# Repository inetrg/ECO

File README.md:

# Source Files for the ECO Sensor Box
The ECO sensor box is a versatile modular wireless sensor box for perpetual operation based on energy harvesting.
Using a self-adaptive power management the sensor self-adapts its power consumption according to energy availability,
based on real-time, online self measurement of its power consumption and availability.

This repository contains source and design files required to build your own ECO-enabled sensor box.
The initial version of the ECO box used separate independent modules which you can find in corresponding subfolders.
The newer version uses a more integrated approach by placing most of the subsystems onto a single PCB for easier setup.

## ECO Box Design Files
Below we list some notes on what to consider when working with the ECO Box design files.

## Tools and Files
All design files are being processed only using open source tools to make them accessible and reusable for everyone.

KiCAD is used for schematics and Layout of the custom PCB.
FreeCAD is used for mechanical design of the physical box assembly, including the enclosure, PCB, external sensors, antenna, etc.
Blender is used for further visualization/rendering purposes (custom materials, lighting etc.) for more sophisticated controls of visuals.

To exchange data between all these tools different formats are used and some of them need workarounds to make everything work as expected.

### FreeCAD -> KiCAD
As mentioned, FreeCAD is used for the mechanical part. So an easy way to get a fitting PCB outline for a given enclosure is to export the outline from there to KiCAD.
For this the DXF 2D export of FreeCAD is used and the exported drawing is then imported to the edge.cuts layer in KiCAD before doing the PCB layout.

For custom components that don't have a 3D-Symbol in KiCAD, we also use FreeCAD to desing them and use the STEP export to use them in KiCAD.

### KiCAD -> FreeCAD
With the PCB being done the whole PCB including associated 3D models for components can be imported from the *.kicad_pcb file using the KiCADStepUp Workbench of FreeCAD.
For this the "Load KiCAD PCB and Board Parts" was used.
A special case that required a workaround here was the "Add Tracks" feature that didn't work well and made FreeCAD crash frequently.
Instead the Tracks were exported to DXF from KiCAD and then imported using the "Add Silks" feature (custom colors can still be appied later on).

In FreeCAD any missing mechanical design can then be aligned around the PCB and its components.

### FreeCAD -> Blender
To export the whole model from FreeCAD to blender the format that worked best for us is *gltf.
However, there is a problem with colors/materials that are only applied to faces (instead of whole objects) and if exported directly to gltf the colors will disappear.
A workaround for that is to first export to "STEP with colors" then import to FreeCAD again, an then do the export to gltf for blender. This way the colors that are present on KiCAD models don't get lost.

# Third Party Material
Some CAD models of PCB components and the assembly design use third party material from [SnapEDA](https://www.snapeda.com/) and [GrabCAD](https://grabcad.com).

# Further Information
Firmware sources can be found in a [separate repository](https://github.com/inetrg/ECO-fw).
For more information also visit our [project website](https://eco.riot-apps.net).

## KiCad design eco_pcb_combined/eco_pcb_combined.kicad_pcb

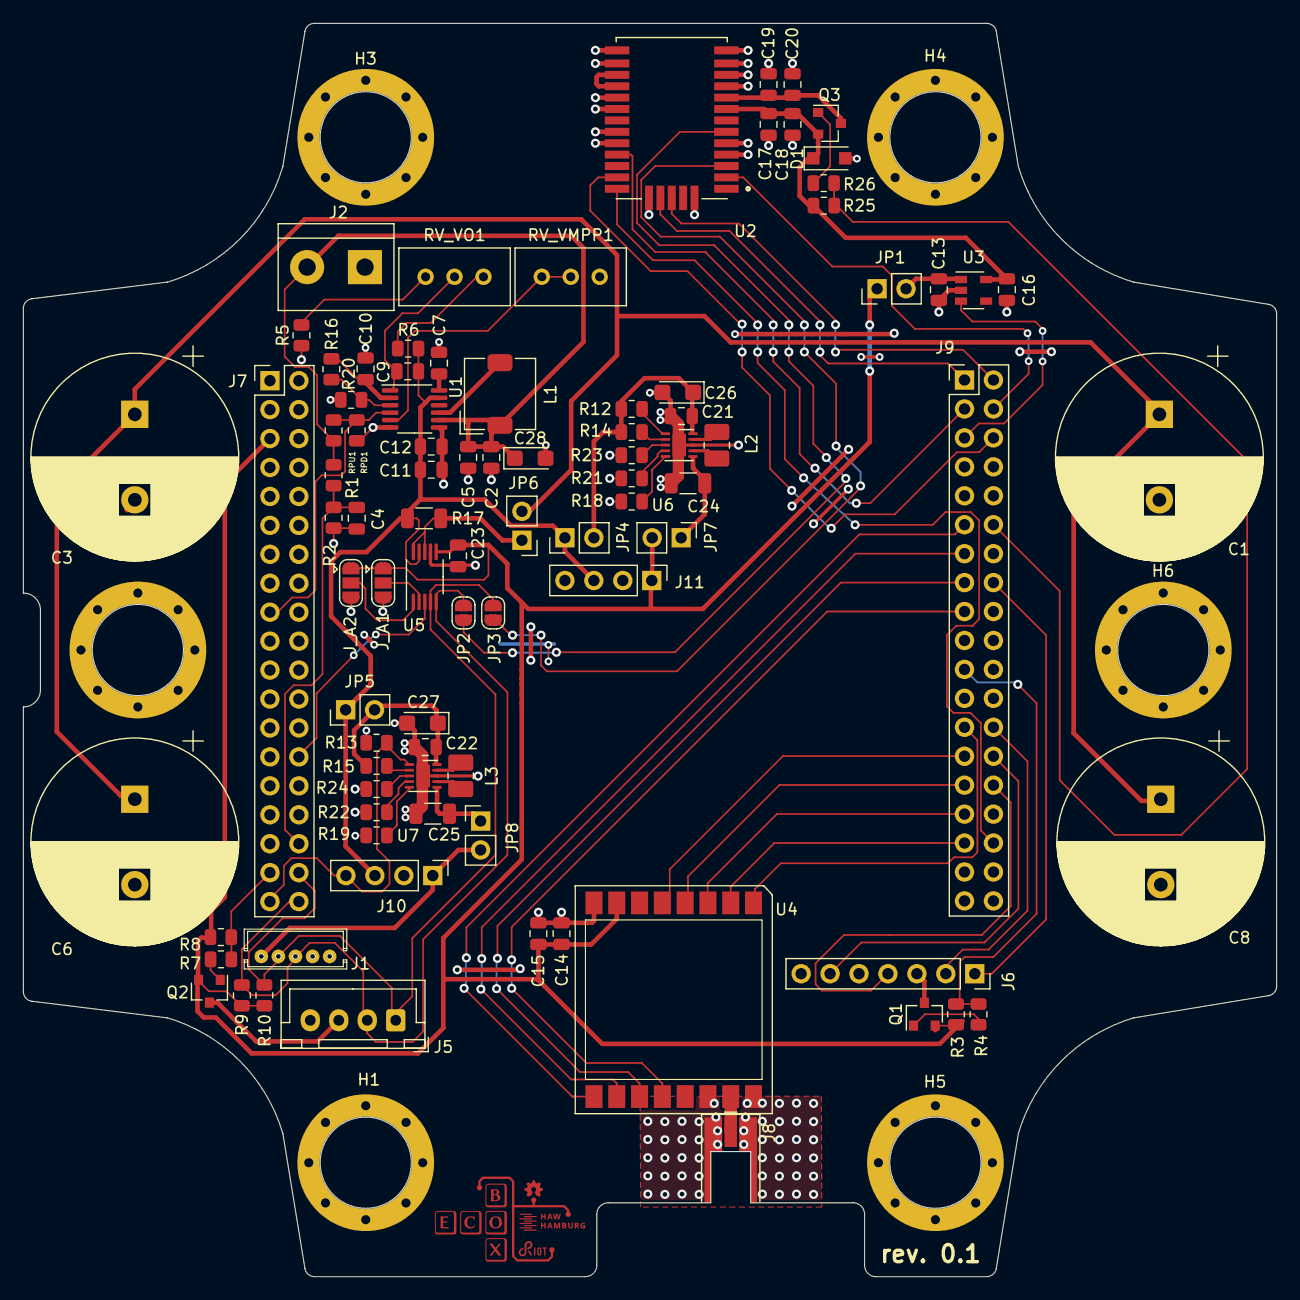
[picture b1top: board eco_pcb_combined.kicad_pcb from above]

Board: 2 copper layers, 110.0 x 110.0 mm, 97 parts (1 on the bottom side), 75 nets.

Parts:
C1, C3, C6, C8: 50F-100F; CP_Radial_D18.0mm_P7.50mm
C2, C11, C14, C20, C21, C22: 10µF; C_0805_2012Metric
C4: 1nF; C_0805_2012Metric
C5, C7, C12, C13, C16: 1µF; C_0805_2012Metric
C9: 22pF; C_0805_2012Metric
C10, C18: 4.7µF; C_0805_2012Metric
C15, C17, C19, C23: 100nF; C_0805_2012Metric
C24, C25: 22µF; C_1206_3216Metric
C26, C27, C28: 47µF; CP_EIA-3216-10_Kemet-I
D1: Littlefuse_TVS_SMF3.3; D_SOD-123F
H1, H2, H3, H4, H5, H6: MountingHole; MountingHole_8.1mm_M8_Pad_Via
J1: Conn_01x05; JST_B5B_ZR
J2: Screw_Terminal_01x02; TerminalBlock_bornier-2_P5.08mm
J5: Conn_01x04; JST_XH_B4B-XH-A_1x04_P2.50mm_Vertical
J6: BOB-00544; PinSocket_1x07_P2.54mm_Vertical
J7, J9: Conn_02x19_Odd_Even; PinHeader_2x19_P2.54mm_Vertical
J8: Conn_Coaxial; MMCX_Molex_73415-0961_Horizontal_1.6mm-PCB
J10, J11: Conn_01x04_Female; PinHeader_1x04_P2.54mm_Vertical
JP1, JP4, JP5, JP6, JP7, JP8: Jumper_2_Bridged; PinHeader_1x02_P2.54mm_Vertical
JP2, JP3: Jumper_NC_Small; SolderJumper-2_P1.3mm_Open_RoundedPad1.0x1.5mm
J_A1, J_A2: JP2E; SolderJumper-3_P1.3mm_Open_RoundedPad1.0x1.5mm
L1: 10µH; L_TDK_SLF6045
L2, L3: 2.2µH; L_1008_2520Metric_Pad1.43x2.20mm_HandSolder
LOGO1: Logo; RIOT_ECO_HAW_OSHW_straight
Q1, Q2, Q3: Si2329DS; SOT-23
R1, R16: 1MΩ; R_0805_2012Metric
R2, R5: 390kΩ; R_0805_2012Metric
R3, R8, R12, R13, R14, R15, R26: 100kΩ; R_0805_2012Metric
R4, R7, R25: 330Ω; R_0805_2012Metric
R6: 1.1MΩ; R_0805_2012Metric
R9, R10: 4.7kΩ; R_0805_2012Metric
R17: 0.27Ω; R_1206_3216Metric
R18, R19, R21, R22: 0Ω; R_0805_2012Metric
R20: 2.5MΩ; R_0805_2012Metric
R23, R24: 36.5kΩ; R_0805_2012Metric
RPD1: 100kΩ; R_0805_2012Metric
RPU1: 100kΩ; R_0805_2012Metric
RV_VMPP1: 500kΩ; Potentiometer_Bourns_3296W_Vertical
RV_VO1: 500kΩ; Potentiometer_Bourns_3296W_Vertical
U1: LTC3105; MSOP-12_3x4mm_P0.65mm
U2: L96; XCVR_L96
U3: TPS7A0230PDBVR; SOT-23-5
U4: DORJI_DRF1276G; DRF1276G
U5: INA226INA226AIDGS; VSSOP-10_3x3mm_P0.5mm
U6, U7: TPS63900; WSON-10-1EP_2.5x2.5mm_P0.5mm_EP1.2x2mm

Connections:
3V3: C14.2, C15.2, C23.2, J7.5, J11.1, JP1.1, JP7.2, J_A1.1, J_A2.1, Q1.2, Q2.2, R3.1, R8.1, R9.1, R10.1, U4.7, U5.6
3V3_EXT_I2C: J5.3, Q2.3
3V3_SDCARD: J6.3, Q1.3
3V_GPS: C16.2, C17.2, C18.2, D1.1, Q3.2, R26.1, U2.8, U3.5
5V: J1.5, J10.1, JP8.2
/IN+: JP6.1, R17.2, U5.8, U5.10
A0_PA0_WKUP1|INA_ALERT: J7.28, U5.3
A3_PB0|PV_OCV_SENSE: C4.2, J7.34, R1.1, R2.2
D2_PA10|LORA_DIO0: J9.33, U4.2
D3_PB3|LORA_DIO1: J9.31, U4.3
D4_PB5|LORA_DIO2: J9.29, U4.4
D5_PB4|LORA_DIO3: J9.27, U4.5
D6_PB10|LORA_RESET: J9.25, U4.1
D8_PA9|SDCARD_PWR_SW: J9.21, R3.2, R4.1
D10_PB6|LORA_CS: J9.17, U4.12
D11_PA7|LORA_MOSI: J9.15, U4.11
D12_PA6|LORA_MISO: J9.13, U4.10
D13_PA5|LORA_SCK_LED2: J9.11, U4.9
FBLDO: R16.1, R20.2, U1.3
GND: C1.2, C2.2, C3.2, C4.1, C5.2, C6.2, C7.1, C8.2, C10.1, C11.1, C12.1, C13.1, C14.1, C15.1, C16.1, C17.1, C18.1, C19.1, C20.1, C21.1, C22.1, C23.1, C24.1, C25.1, C26.2, C27.2, C28.2, D1.2, J1.1, J1.2, J2.1, J5.4, J6.5, J7.8, J7.19, J7.20, J7.22, J8.2, J9.9, J9.20, J10.2, J11.2, J_A1.3, J_A2.3, R2.1, R5.1, R13.2, R18.1, R19.1, R20.1, R21.1, R22.1, R23.1, R24.1, RPD1.2, RV_VMPP1.1, U1.6, U1.7, U2.4, U2.5, U2.10, U2.11, U2.12, U2.13, U2.14, U2.15, U2.18, U2.19, U2.21, U2.22, U2.27, U2.31, U3.2, U4.8, U4.14, U4.16, U5.7, U6.8, U6.11, U7.8, U7.11
LDO: C10.2, R16.2, U1.2
LORA_ANT: J8.1, U4.15
unnamed: C7.2, U1.12
unnamed: C9.1, RV_VO1.2, U1.1
unnamed: C13.2, JP1.2, U3.1
unnamed: C19.2, C20.2, Q3.3, U2.9
unnamed: C21.2, C26.1, JP4.2, R12.2, R14.2, U6.10
unnamed: C22.2, C27.1, JP5.2, R15.2, U7.10
unnamed: C24.2, JP7.1, U6.6
unnamed: C25.2, JP8.1, U7.6
unnamed: JP2.2, U2.6
unnamed: JP3.2, U2.3
unnamed: J_A1.2, U5.2
unnamed: J_A2.2, U5.1
unnamed: L1.2, U1.9
unnamed: L2.1, U6.7
unnamed: L2.2, U6.9
unnamed: L3.1, U7.7
unnamed: L3.2, U7.9
unnamed: Q1.1, R4.2
unnamed: Q2.1, R7.2
unnamed: Q3.1, R25.2
unnamed: R5.2, RV_VO1.3
unnamed: R6.2, RV_VO1.1
unnamed: R12.1, U6.1
unnamed: R14.1, U6.2
unnamed: R15.1, U7.2
unnamed: R18.2, U6.5
unnamed: R19.2, U7.5
unnamed: R21.2, U6.4
unnamed: R22.2, U7.4
unnamed: R23.2, U6.3
unnamed: R24.2, U7.3
unnamed: RV_VMPP1.2, RV_VMPP1.3, U1.5
unnamed: U2.16, U2.17
PA12: J9.12, R25.1, R26.2
PA15|LTC_SHDN: J7.17, RPD1.1, RPU1.1, U1.4
PB8_D15|GPS_NRESET: J9.3, U2.23
PB9_D14|GPS_SUP_EN: J9.5, U3.3
PB12|SDCARD_CS: J6.1, J9.16
PB13|SDCARD_SCK: J6.4, J9.30
PB14|SDCARD_MISO: J6.6, J9.28
PB15|SDCARD_MOSI: J6.2, J9.26
PC0|I2C_SCL: J1.3, J5.2, J7.38, JP2.1, R9.2, U5.5
PC1|I2C_SDA: J1.4, J5.1, J7.36, JP3.1, R10.2, U5.4
PC2|EXT_SENS_3V3_SW: J7.35, R7.1, R8.2
PC3|5V_EN: J7.37, J10.4, R13.1, U7.1
PC4|GPS_UART_RX_U1TX: J9.34, U2.26
PC5|GPS_UART_TX_U1RX_WKUP5: J9.6, U2.25
PC6|GPS_3D_FIX: J9.4, U2.2
PC8|GPS_TIME_PULSE: J9.2, U2.29
PC9|GPS_FORCE_ON: J9.1, U2.28
PV+: C2.1, C5.1, C28.1, J2.2, L1.1, R1.2, RPU1.2, U1.8
VSC: C1.1, C3.1, C6.1, C8.1, JP6.2
V_CHGREG: C9.2, C11.2, C12.2, J10.3, J11.3, JP4.1, JP5.1, R6.1, R17.1, U1.11, U5.9

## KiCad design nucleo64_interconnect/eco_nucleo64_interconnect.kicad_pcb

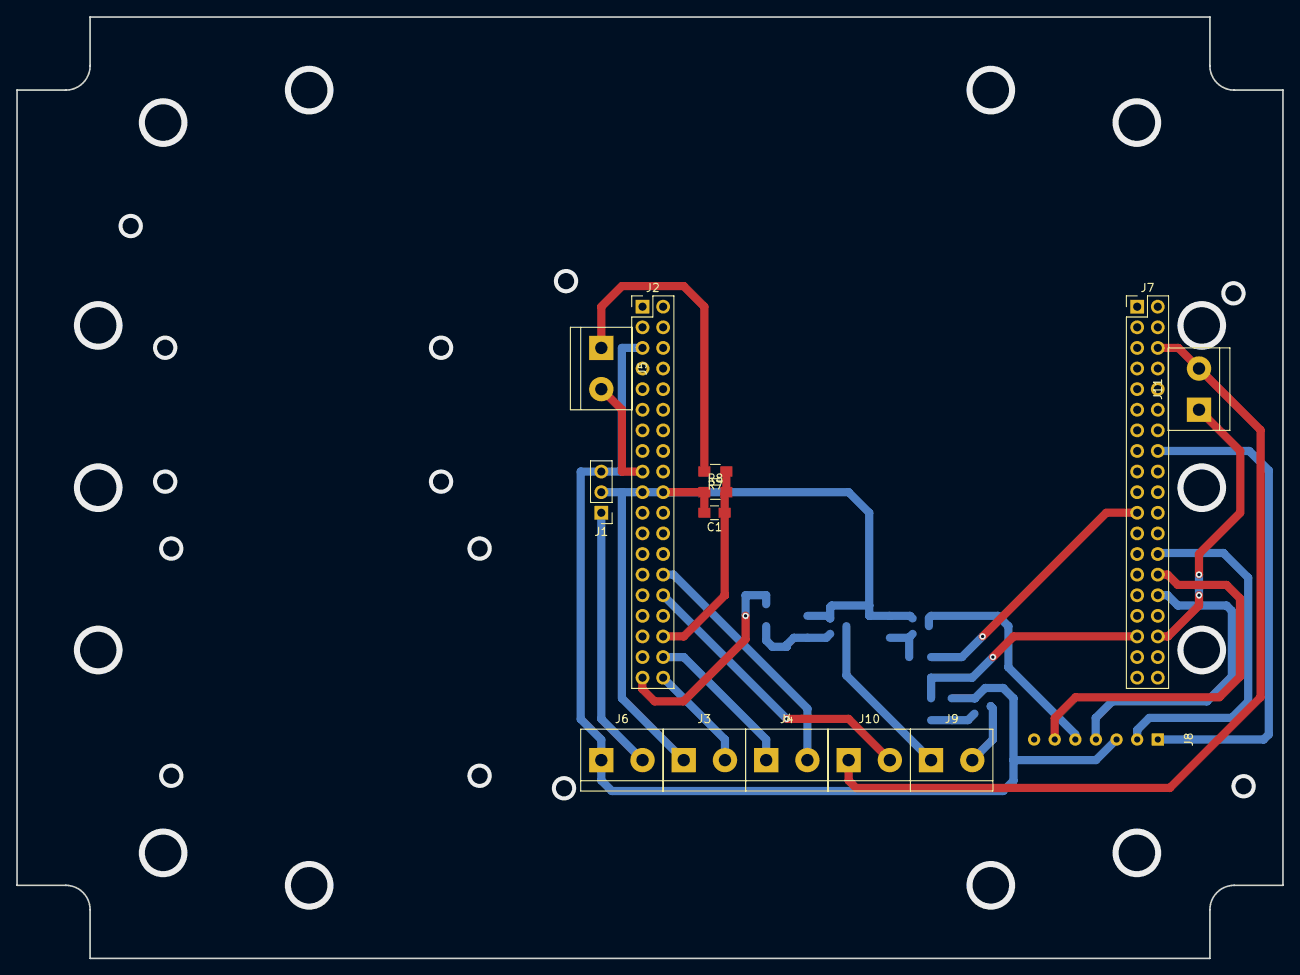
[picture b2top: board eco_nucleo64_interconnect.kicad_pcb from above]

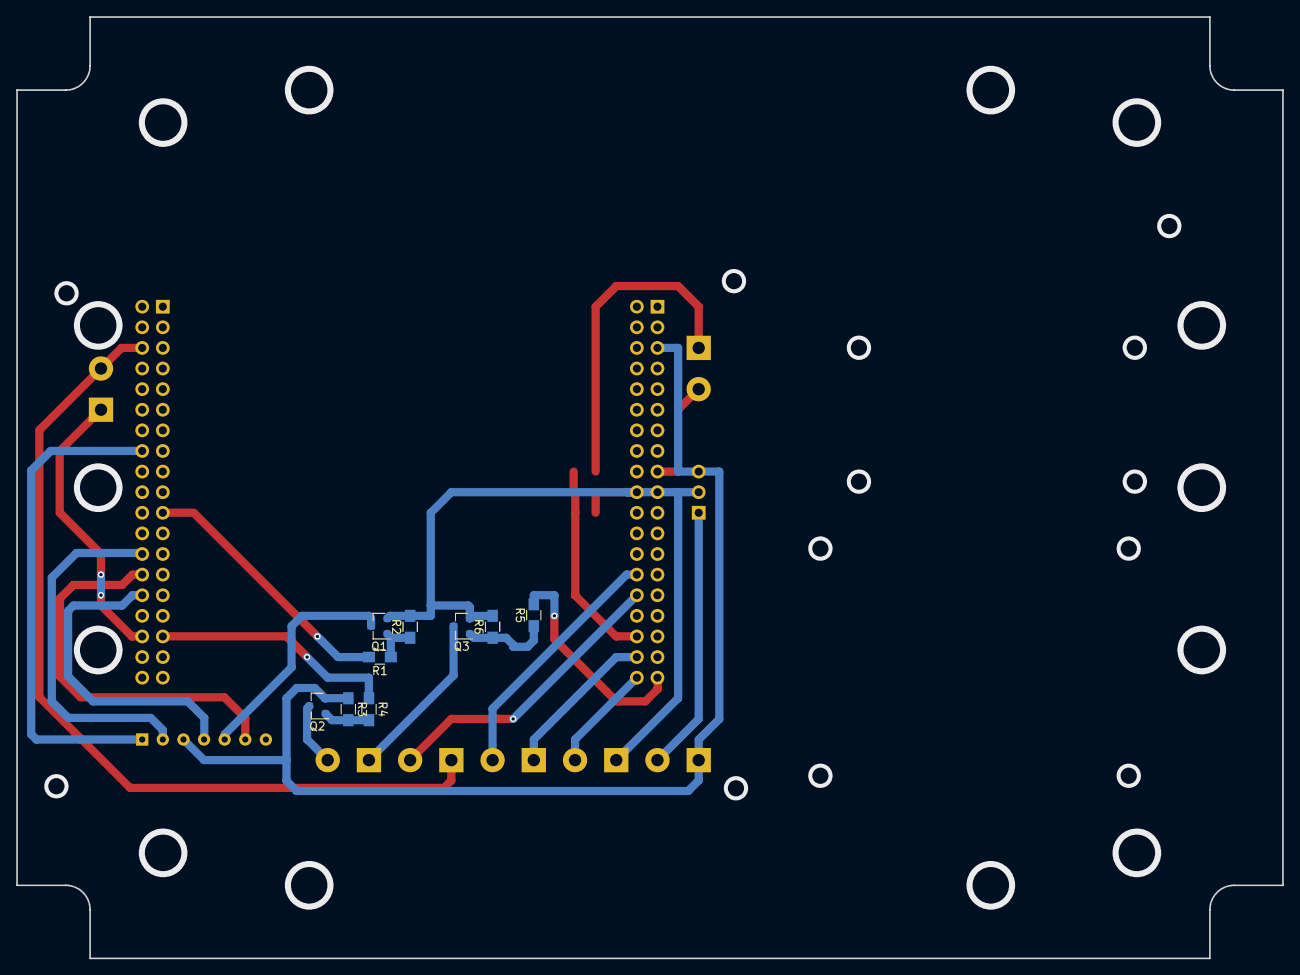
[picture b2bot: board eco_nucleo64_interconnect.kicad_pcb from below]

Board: 2 copper layers, 156.0 x 116.0 mm, 23 parts (9 on the bottom side), 25 nets.

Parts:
C1: 1n; C_0805_HandSoldering
J1: Conn_01x03; Pin_Header_Straight_1x03_Pitch2.54mm
J2, J7: Conn_02x19_Odd_Even; Pin_Header_Straight_2x19_Pitch2.54mm
J3, J4, J5, J6, J9, J10, J11: Screw_Terminal_01x02; TerminalBlock_bornier-2_P5.08mm
J8: BOB-00544
Q1, Q3: BSS138; SOT-23
Q2: NTR2101P; SOT-23
R1, R2, R3, R4, R5, R6: R; R_0805_HandSoldering
R7: 1M; R_0805_HandSoldering
R8: 390k; R_0805_HandSoldering

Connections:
3V3: J1.3, J2.5, J6.1, J8.3, Q2.2, R3.1
3V3_SWITCHED: J9.2, Q2.3
A0_PA0_WKUP1: J2.28, J4.2
A1_PA1|GPAD: J2.30, J10.2
A3_PB0|PV_SENSE: C1.1, J2.34, R7.1, R8.2
CS_PB12|SD-CS: J7.16, J8.1
D2_PA10|GP-3V3-SW: J7.33, R4.1
D8_PA9|SD-PWR-SW: J7.21, R1.2
GND: C1.2, J1.2, J2.19, J2.20, J3.1, Q1.2, Q3.2, R2.2, R6.2, R8.1
GND_SWITCHED: J9.1, Q3.3
MISO_PB14|SD-DO: J7.28, J8.6
MOSI_PB15|SD-DI: J7.26, J8.2
unnamed: J8.5, Q1.3
unnamed: Q1.1, R1.1, R2.1
unnamed: Q2.1, R3.2, R4.2
unnamed: Q3.1, R5.1, R6.1
PA15|LTC_SHDN: J2.17, J5.2
PC0_SCL: J2.38, J3.2
PC1_SDA: J2.36, J4.1
PC3|GP-GND-SW: J2.37, R5.2
PC4_U1TX: J7.34, J11.1
PC5_U1RX_WKUP5|GPD: J7.6, J10.1, J11.2
PV+: J5.1, R7.2
SCK_PB13|SD-SCK: J7.30, J8.4
VIN: J1.1, J6.2

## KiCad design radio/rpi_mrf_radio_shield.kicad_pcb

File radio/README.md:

# Adapter PCB to connect a [rpi802154-r1](http://openlabs.co/OSHW/Raspberry-Pi-802.15.4-radio) or [MRF24J40MA](http://www.microchip.com/wwwproducts/en/MRF24J40MA) module to nucleo / arduino boards

This simple shield can be used to connect the aforementioned radio modules to STM32 based boards like the [Nucleo-64 family](http://www.st.com/resource/en/user_manual/dm00105823.pdf) or various other boards that come with the well known arduino header.

The main reason for creating this shield is that I need a switch to disconnect the modules from their power supply in order to get rid of small leakage currents that occur even in sleep mode. This is done using a low side n-channel mosfet. Another point is that I need to do this for a few devices and I want them to have a more sturdy connection than the usual (error prone) breadboard and jumper wire tinkerng. Think: plug&play instead of fiddling with loose wires and always looking up pin configurations again.

While tossing together a custom shield, why not add some little features that can be used for demo applications? For this there are two LEDs (D_PWR_1 and D_ACT1) connected to the radio's supply voltage and the CS pin to display if the device is powered and active. This allows to easily visualize duty-cycling applications.
Keeping in mind the initial purpose (low-power) the LEDs can be disconnected using the jumpers JP1 and JP2.

As a quick reference this is how the pins are connected:

| rpi802154-r1    | MRF24J40MA    | Nucleo Pin (name / connector) | Arduino Pin Name  |
|-----------------|---------------|-------------------------------|-------------------|
| +3.3V (2)       | Vin (10)      | +3V3 / CN6[4]                 | +3V3              |
| GND (6,10)      | GND (1,11,12) | *GND  / CN6[6,7], CN5[7]**    | GND               |
| MISO (4)        | SDO (7)       | PA6  / CN5[5]                 | D12               |
| MOSI (3)        | SDI (5)       | PA7  / CN5[4]                 | D11               |
| AT86_SEL (8)    | CS  (8)       | PB6  / CN5[3]                 | D10               |
| AT96_IRQ (12)   | INT (4)       | PA8  / CN9[8]                 | D7                |
| AT96_SLP_TR (9) | WAKE (3)      | PB10 / CN9[7]                 | D6                |
| AT96_RST (11)   | RESET (2)     | PB4  / CN9[6]                 | D5                |
| SCK (5)         | SCK (6)       | PA5  / CN5[6]                 | D13               |

\* The GND of the radios are actually connected to the drain pad of the FET which in turn has its source pad connected to GND of the board.

| Additional function      | Nucleo Pin (name / connector) | Arduino Pin Name  |
|--------------------------|-------------------------------|-------------------|
| FET drain (SOT-23 pad 1) | PA4  / CN8[3]                 | A2                |

---
## BOM

Below is the bill of materials for equipping the pcb. Obviously you can choose to use other parts as long as they have the same footprint and properties. For the lazy ones: you may want to look at [this pre-filled shopping cart at Mouser](https://www.mouser.com/ProjectManager/ProjectDetail.aspx?AccessID=bb2e666ecb) which contains all the parts needed to equip a single PCB.

| Component identifier      | Part                               | cnt. | Mouser Link                                                                      |
|---------------------------|------------------------------------|------|----------------------------------------------------------------------------------|
| J1, J2                    | 1x6 Pin Header 2.54mm pitch female | 2    | [PMV20XNEA](https://www.mouser.com/ds/2/302/PMV20XNEA-1151838.pdf)               |
| J3, J5                    | 1x8 Pin Header 2.54mm pitch male   | 2    | [855-M20-7820646](https://www.mouser.de/ProductDetail/855-M20-7820646)           |
| J4                        | 1x10 Pin Header 2.54mm pitch male  | 1    | [538-22-28-4102](https://www.mouser.de/ProductDetail/538-22-28-4102)             |
| J6                        | 1x6 Pin Header 2.54mm pitch male   | 1    | [538-22-28-4062](https://www.mouser.de/ProductDetail/538-22-28-4062)             |
| J7                        | 2x6 Pin Header 2.54mm pitch male   | 2    | [571-103777-3](https://www.mouser.de/ProductDetail/571-103777-3)                 |
| JP1, JP2                  | 1x2 Pin Header 2.54mm pitch male   | 2    | [571-826936-2](https://www.mouser.de/ProductDetail/571-826936-2)                 |
| -                         | Jumpers for JP1 and JP2            | 2    | [571-826936-2](https://www.mouser.de/ProductDetail/571-826936-2)                 |
| Q1                        | SOT-23 n-channel MOSFET            | 1    | [151-8010-E](https://www.mouser.de/ProductDetail/151-8010-E)                     |
| R1, R2                    | 1.5k 0805 SMD resistor             | 2    | [652-CR0805FX-1501ELF](https://www.mouser.de/ProductDetail/652-CR0805FX-1501ELF) |
| R3                        | 8.2k 0805 SMD resistor             | 1    | [652-CR0805JW-822ELF](https://www.mouser.de/ProductDetail/652-CR0805JW-822ELF)   |
| R4, R5 (only one needed)  | 47k 0805 SMD resistor              | 1    | [71-CRCW0805-47K-E3](https://www.mouser.de/ProductDetail/71-CRCW0805-47K-E3)     |
| D_PWR_1, D_PWR_1          | 0805 SMD LED                       | 2    | [604-AP2012EC](https://www.mouser.de/ProductDetail/604-AP2012EC)                 |

---
## Configuration

To define your prefered default state of the supply switch you can either fit a pull-up resistor to R5 or a pull-down to R4. While this is true for the FET listed in the BOM above, using another FET might reverse the logic and/or need other resistor values to work properly.

| Setting                   | Configuration             |
|---------------------------|---------------------------|
| Radio powered by default  | R4=not fitted / R5=47k    |
| Radio disabled by default | R4=47k / R5=not fitted    |
| LED D_PWR_1 disabled      | JP1=open                  |
| LED D_ACT1 disabled       | JP2=open                  |

---
### Using this shield with [RIOT](https://github.com/RIOT-OS/RIOT)
Depending on which module you want to use, copy one of the the following blocks to your applications Makefile.

**Note:**  Currently RIOT (more specifically it's radio driver(s)) doesn't handle power enable pins for the radios. This implies that you need to take care of enabling/disabling (and by that also initializing) the radio *manually*, wehen the R4/R5 pull resistors are configured to disable the supply by default.
Using RIOT's auto-init feature together with "radio disabled by default" configuration will not work out of the box unless you add the needed power-on functionality to the beginning of the drivers init-function. As an alternative you can also just disable auto_init.

```
USEMODULE += mrf24j40
CFLAGS += -DMRF24J40_PARAM_SPI=SPI_DEV\(0\)
CFLAGS += -DMRF24J40_PARAM_SPI_CLK=SPI_CLK_5MHZ
CFLAGS += -DMRF24J40_PARAM_CS=GPIO_PIN\(1,6\)
CFLAGS += -DMRF24J40_PARAM_INT=GPIO_PIN\(0,8\)
CFLAGS += -DMRF24J40_PARAM_RESET=GPIO_PIN\(1,4\)

CFLAGS += -DRADIO_SUPPLY_SWITCH_PINT=GPIO_PIN\(0,4\)
```

```
USEMODULE += at86rf2xx
CFLAGS += -DAT86RF2XX_PARAM_SPI=SPI_DEV\(0\)
CFLAGS += -DAT86RF2XX_PARAM_SPI_CLK=SPI_CLK_5MHZ
CFLAGS += -DAT86RF2XX_PARAM_CS=GPIO_PIN\(1,6\)
CFLAGS += -DAT86RF2XX_PARAM_INT=GPIO_PIN\(0,8\)
CFLAGS += -DAT86RF2XX_PARAM_SLEEP=GPIO_PIN\(1,10\)
CFLAGS += -DAT86RF2XX_PARAM_RESET=GPIO_PIN\(1,4\)

CFLAGS += -DRADIO_SUPPLY_SWITCH_PINT=GPIO_PIN\(0,4\)
```

---

(c) by Michel Rottleuthner
The files in this folder are licensed under a Creative Commons Attribution 4.0 International License.
You should have received a copy of the license along with this work. If not, see .

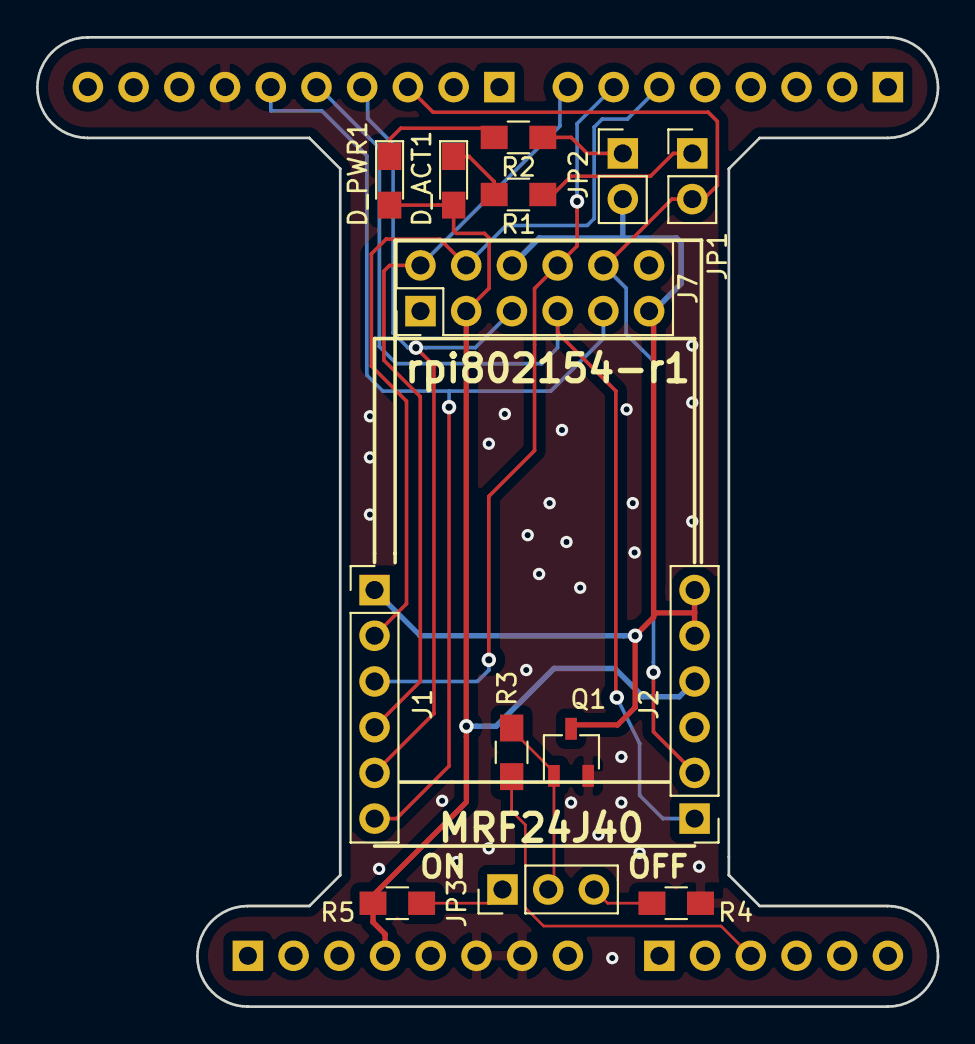
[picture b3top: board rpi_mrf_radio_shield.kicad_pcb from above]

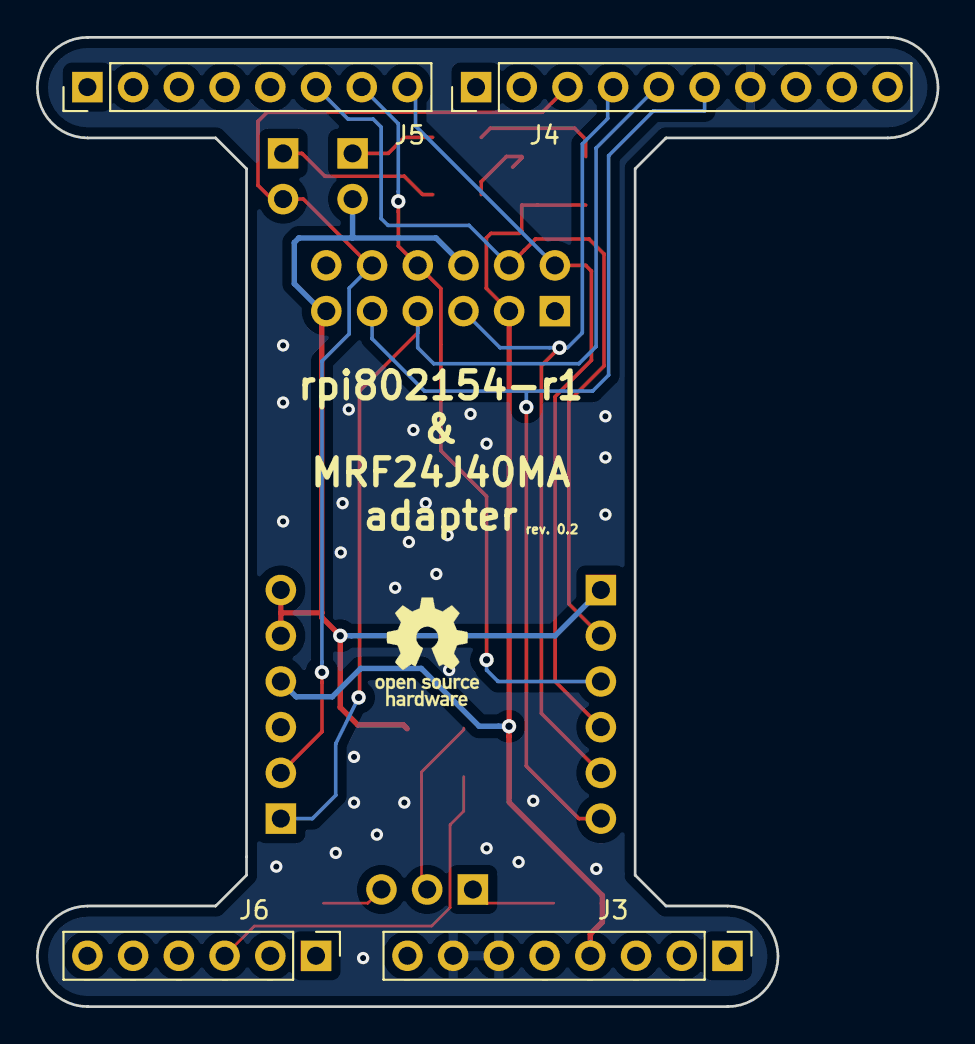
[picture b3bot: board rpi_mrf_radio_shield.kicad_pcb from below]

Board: 2 copper layers, 50.0 x 53.8 mm, 19 parts (5 on the bottom side), 18 nets.

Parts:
D_ACT1: LED; LED_0805_HandSoldering
D_PWR1: LED; LED_0805_HandSoldering
J1, J2: Conn_01x06_Female; Pin_Header_Straight_1x06_Pitch2.54mm
J3, J5: Conn_01x08_Male; Pin_Header_Straight_1x08_Pitch2.54mm
J4: Conn_01x10_Male; Pin_Header_Straight_1x10_Pitch2.54mm
J6: Conn_01x06_Male; Pin_Header_Straight_1x06_Pitch2.54mm
J7: Conn_02x06_Odd_Even; Pin_Header_Straight_2x06_Pitch2.54mm
JP1, JP2: Jumper; Pin_Header_Straight_1x02_Pitch2.54mm
JP3: J_on_off; Pin_Header_Straight_1x03_Pitch2.54mm
LOGO1: Logo_Open_Hardware_Small; OSHW-Logo_5.7x6mm_SilkScreen
Q1: MMBF170; TSOT-23
R1, R2: 1.5k; R_0805_HandSoldering
R3: 8k; R_0805_HandSoldering
R4: 47k; R_0805_HandSoldering
R5: <inf>k; R_0805_HandSoldering

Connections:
CS: J2.2, J4.3, J7.10, JP1.2
FET_D: J1.1, J2.5, J2.6, J7.6, J7.11, JP2.2, Q1.3
GND: J3.6, J3.7, J4.7, Q1.2, R4.1
INT: J1.4, J5.8, J7.2
MCU_SW: J6.3, R3.1
MISO: J2.1, J4.5, J7.7
MOSI: J1.5, J4.4, J7.5
unnamed: D_ACT1.1, R1.2
unnamed: D_PWR1.1, R2.2
unnamed: JP1.1, R1.1
unnamed: JP2.1, R2.1
unnamed: JP3.1, R5.1
unnamed: JP3.2, Q1.1, R3.2
unnamed: JP3.3, R4.2
RST: J1.2, J5.6, J7.4
SCK: J1.6, J4.6, J7.9
VCC: D_ACT1.2, D_PWR1.2, J2.4, J3.4, J7.3, R5.2
WAKE: J1.3, J5.7, J7.8

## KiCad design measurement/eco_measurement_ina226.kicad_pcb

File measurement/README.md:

# RIOT Energy-Harvesting Monitor using INA226

This module can be used to measure voltage and current of a connected load.
It comes with three different measurement ranges that can be freely configured by mounting different shunt resistors.
Depending on your use case you can switch between the measurement ranges with the slider switches.
The configuration of the board hosts jumpers to configure four different I2C slave addresses.

---
## BOM

Below is the bill of materials for equipping the pcb. Obviously you can choose to use other parts as long as they have the same footprint and properties. For the lazy ones: you may want to look at [this pre-filled shopping cart at Mouser](https://www.mouser.com/ProjectManager/ProjectDetail.aspx?AccessID=cd3d5edc18) which contains all the parts needed to equip a single PCB.

| Component identifier      | Part                                | cnt. | Mouser Link                                                                      |
|---------------------------|-------------------------------------|------|----------------------------------------------------------------------------------|
| U1                        | INA226 VSSOP-10                     | 1    | [595-INA226AIDGSR](https://www.mouser.de/ProductDetail/595-INA226AIDGSR)         |
| SW1, SW2, SW3             | Slide Switches SPDT 4A 125V         | 3    | [642-25136NAH ](https://www.mouser.de/ProductDetail/642-25136NAH)                |
| R1                        | 0.1 Ohm 0.5% current sense resistor | 1    | [660-SLW1TTER100D](https://www.mouser.de/ProductDetail/660-SLW1TTER100D)         |
| R2                        | 1 Ohm 0.5% current sense resistor   | 1    | [660-SL1TTE1R00D](https://www.mouser.de/ProductDetail/660-SL1TTE1R00D)           |
| R3                        | 2 Ohm 0.5% current sense resistor   | 1    | [660-SL1TTE2R00D](https://www.mouser.de/ProductDetail/660-SL1TTE2R00D)           |
| C1                        | 0.1 µF Capacitor                    | 1    | [77-VJ0805Y104JXXAC](https://www.mouser.de/ProductDetail/77-VJ0805Y104JXXAC)     |
| -                         | Jumper                              | 2    | [151-8010-E](https://www.mouser.de/ProductDetail/151-8010-E)                     |
| X1, X2, X3, X4            | Fixed Terminal screw clamp 2P       | 4    | [504-EM366002](https://www.mouser.de/ProductDetail/504-EM366002)                 |
| JP1, JP1                  | 1x3 Pin Header 2.54mm pitch male    | 2    | [538-22-28-4031](https://www.mouser.de/ProductDetail/538-22-28-4031)             |

---
## Configuration

With the jumpers on JP1 and JP2 you can configure the I2C slave address according to the following table.

| JPA1    | JPA0    | A1 Pin  | A0 Pin  | Address  |
|---------|---------|---------|---------|----------|
|  1 2-3  |  1 2-3  |  GND    |  GND    |  0x40    |
|  1 2-3  |  1-2 3  |  GND    |  VS     |  0x41    |
|  1-2 3  |  1 2-3  |  VS     |  GND    |  0x44    |
|  1-2 3  |  1-2 3  |  VS     |  VS     |  0x45    |

---

(c) by Michel Rottleuthner
The files in this folder are licensed under a Creative Commons Attribution 4.0 International License.
You should have received a copy of the license along with this work. If not, see .

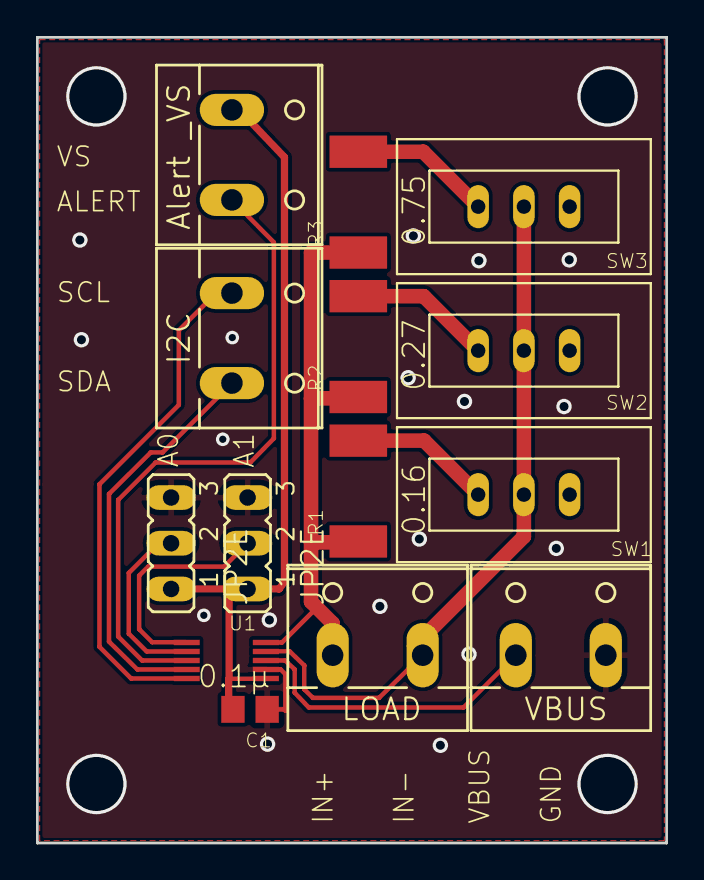
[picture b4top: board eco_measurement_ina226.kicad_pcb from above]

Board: 2 copper layers, 35.0 x 44.8 mm, 14 parts (0 on the bottom side), 13 nets.

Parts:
C1: 0.1µ; C0805
J_A0, J_A1: JP2E; JP2
R1: 0.16; R2512
R2: 0.27; R2512
R3: 0.75; R2512
SW1, SW2, SW3: APEM_SWITCH_25000N25436NAH_3PIN; 25136NAH
U1: INA226INA226AIDGS; INA226_DGS_VSSOP_10
X1: LOAD; W237-102
X2: VBUS; W237-102
X4: Alert _VS; W237-102
X5: I2C; W237-102

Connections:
/IN+: R1.1, R2.1, R3.1, U1.10, X1.1
/IN-: SW1.P$2, SW2.P$2, SW3.P$2, U1.9, X1.2
/R1: R1.2, SW1.P$3
/R2: R2.2, SW2.P$3
/R3: R3.2, SW3.P$3
/VS: C1.2, J_A0.1, J_A1.1, U1.6, X4.1
GND: C1.1, J_A0.3, J_A1.3, U1.7, X2.2
unnamed: J_A0.2, U1.2
unnamed: J_A1.2, U1.1
unnamed: U1.3, X4.2
unnamed: U1.4, X5.2
unnamed: U1.5, X5.1
unnamed: U1.8, X2.1

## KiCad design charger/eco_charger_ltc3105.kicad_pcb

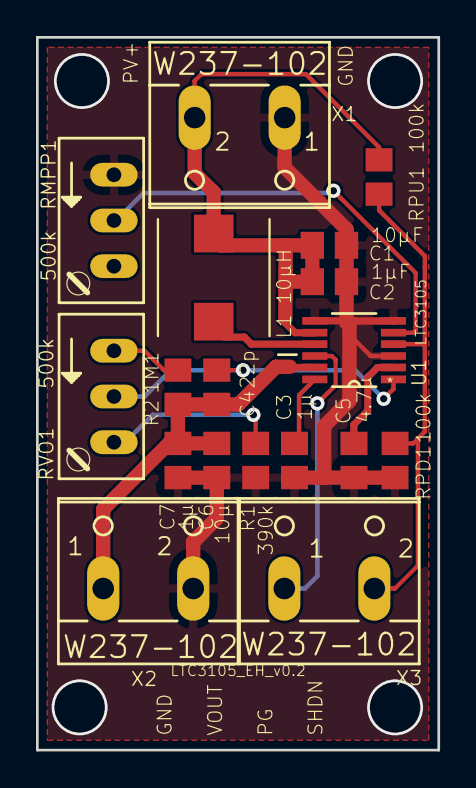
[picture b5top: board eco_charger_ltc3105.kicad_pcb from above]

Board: 2 copper layers, 22.3 x 39.6 mm, 18 parts (0 on the bottom side), 12 nets.

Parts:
C1: 10µF; C0805
C2: 1µF; C0805
C3, C7: 1µ; C0805
C4: 22p; C0805
C5: 4.7µ; C0805
C6: 10µ; C0805
L1: 10µH; TDK_CLF_6045NI-D
R1: 390k; R0805
R2: 1M1; R0805
RMPP1: 500k; RJ9W
RPD1: 100k; R0805
RPU1: 100k; R0805
RVO1: 500k; RJ9W
U1: LTC3105; SOP65P490X110-12N
X1, X2, X3: W237-102

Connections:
/2.2V_LDO: C5.2, U1.2
/PGOOD: U1.10, X3.1
/PV+: C1.2, C2.2, L1.2, RPU1.2, U1.8, X1.2
/SHDN: RPD1.1, RPU1.1, U1.4, X3.2
/VOUT: C4.2, C6.2, C7.2, R2.1, U1.11, X2.1
GND: C1.1, C2.1, C3.1, C5.1, C6.1, C7.1, R1.1, RMPP1.E, RPD1.2, U1.3, U1.6, U1.7, X1.1, X2.2
unnamed: C3.2, U1.12
unnamed: C4.1, RVO1.S, U1.1
unnamed: L1.1, U1.9
unnamed: R1.2, RVO1.A
unnamed: R2.2, RVO1.E
unnamed: RMPP1.S, U1.5

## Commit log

2020-04-17 add .gitignore
2020-04-17 add README
2020-04-17 add sources for charger module
2020-04-17 add sources for measurement module
2020-04-17 add sources for radio module
2020-04-17 add sources for interconnect module
2021-11-11 add freecad and blender files to gitignore
2021-11-11 add pcb design files, libs, and logos of combined board for v2
2021-11-11 add 3d CAD models for box assembly and custom parts
2021-11-11 add blender file that combines KiCAD and FreeCAD models for more advanced postprocessing for visualization
2021-11-11 add Makefile for gerber archive and pinmap generation
2021-11-12 README: update project website link

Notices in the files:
measurement/README.md:
License: CC BY 4.0
